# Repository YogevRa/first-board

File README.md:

# first-board: STM32G431 sensor development board

A 50 × 50 mm, 4-layer development board built around an STM32G431, with a temperature/humidity sensor, USB-C and SWD.
My first PCB: designed in KiCad 10, manufactured and assembled by JLCPCB.

Designed by Yogev Raz.

## Features

- **MCU:** STM32G431CBT6 (Arm Cortex-M4F, 170 MHz, 128 KB flash, 32 KB SRAM), LQFP-48, 12 MHz crystal
- **USB-C:** USB 2.0 full-speed device, USBLC6-2SC6 ESD protection on D+/D−, 5.1 kΩ CC pull-downs
- **Power:** 5 V from USB-C, AP2112K-3.3 LDO (600 mA)
- **Sensor:** Sensirion SHT40 (temperature and humidity, I²C address 0x44), thermally isolated from the rest of the board by an L-shaped slot
- **User I/O:** BOOT, RESET and USER buttons; PWR, STAT and ERR LEDs
- **Headers:** 6-pin SWD (3V3, CLK, GND, DIO, RST, SWO) and 8-pin expansion (3V3, GND, PA2–PA7)
- **Test points:** 5V, GND, 3V3
- **PCB:** 4 layers (signal / GND / 3V3 / signal), 4 × M3 mounting holes

## Documents

- [Schematic (PDF)](docs/first-board.pdf)

## Repository layout

| Path | Contents |
|---|---|
| `first-board.kicad_pro`, `.kicad_sch`, `.kicad_pcb` | KiCad 10 project |
| `first-board.pretty/` | Project footprint library (USB-C receptacle) |
| `first-board.ioc` | STM32CubeMX pin planning |
| `jlcpcb/` | Manufacturing files as sent to JLCPCB: Gerbers and drill files, BOM, CPL |
| `docs/` | Schematic PDF, design specification, renders |

## Manufacturing (v1.0)

- Ordered from JLCPCB in November 2026: 5 PCBs, 2 of them assembled (Economic PCBA)
- 35 SMD parts (16 part types) placed by JLCPCB; the SWD and expansion headers (J2, J3) are hand-soldered
- Rotation offsets between the KiCad footprints and the JLCPCB part library were corrected in the CPL file (U1, U2, U3)
- DRC and ERC clean at release

## Status

- [x] Schematic and layout
- [x] Ordered (v1.0)
- [ ] Bring-up
- [ ] Firmware

## Planned for v1.1

- TVS diode on VBUS and ESD protection on the CC lines
- RC network between the USB shield and GND
- Qwiic (I²C) connector
- Jumper for measuring board current
- Prefer JLCPCB Basic parts, and a stackup that Economic PCBA supports

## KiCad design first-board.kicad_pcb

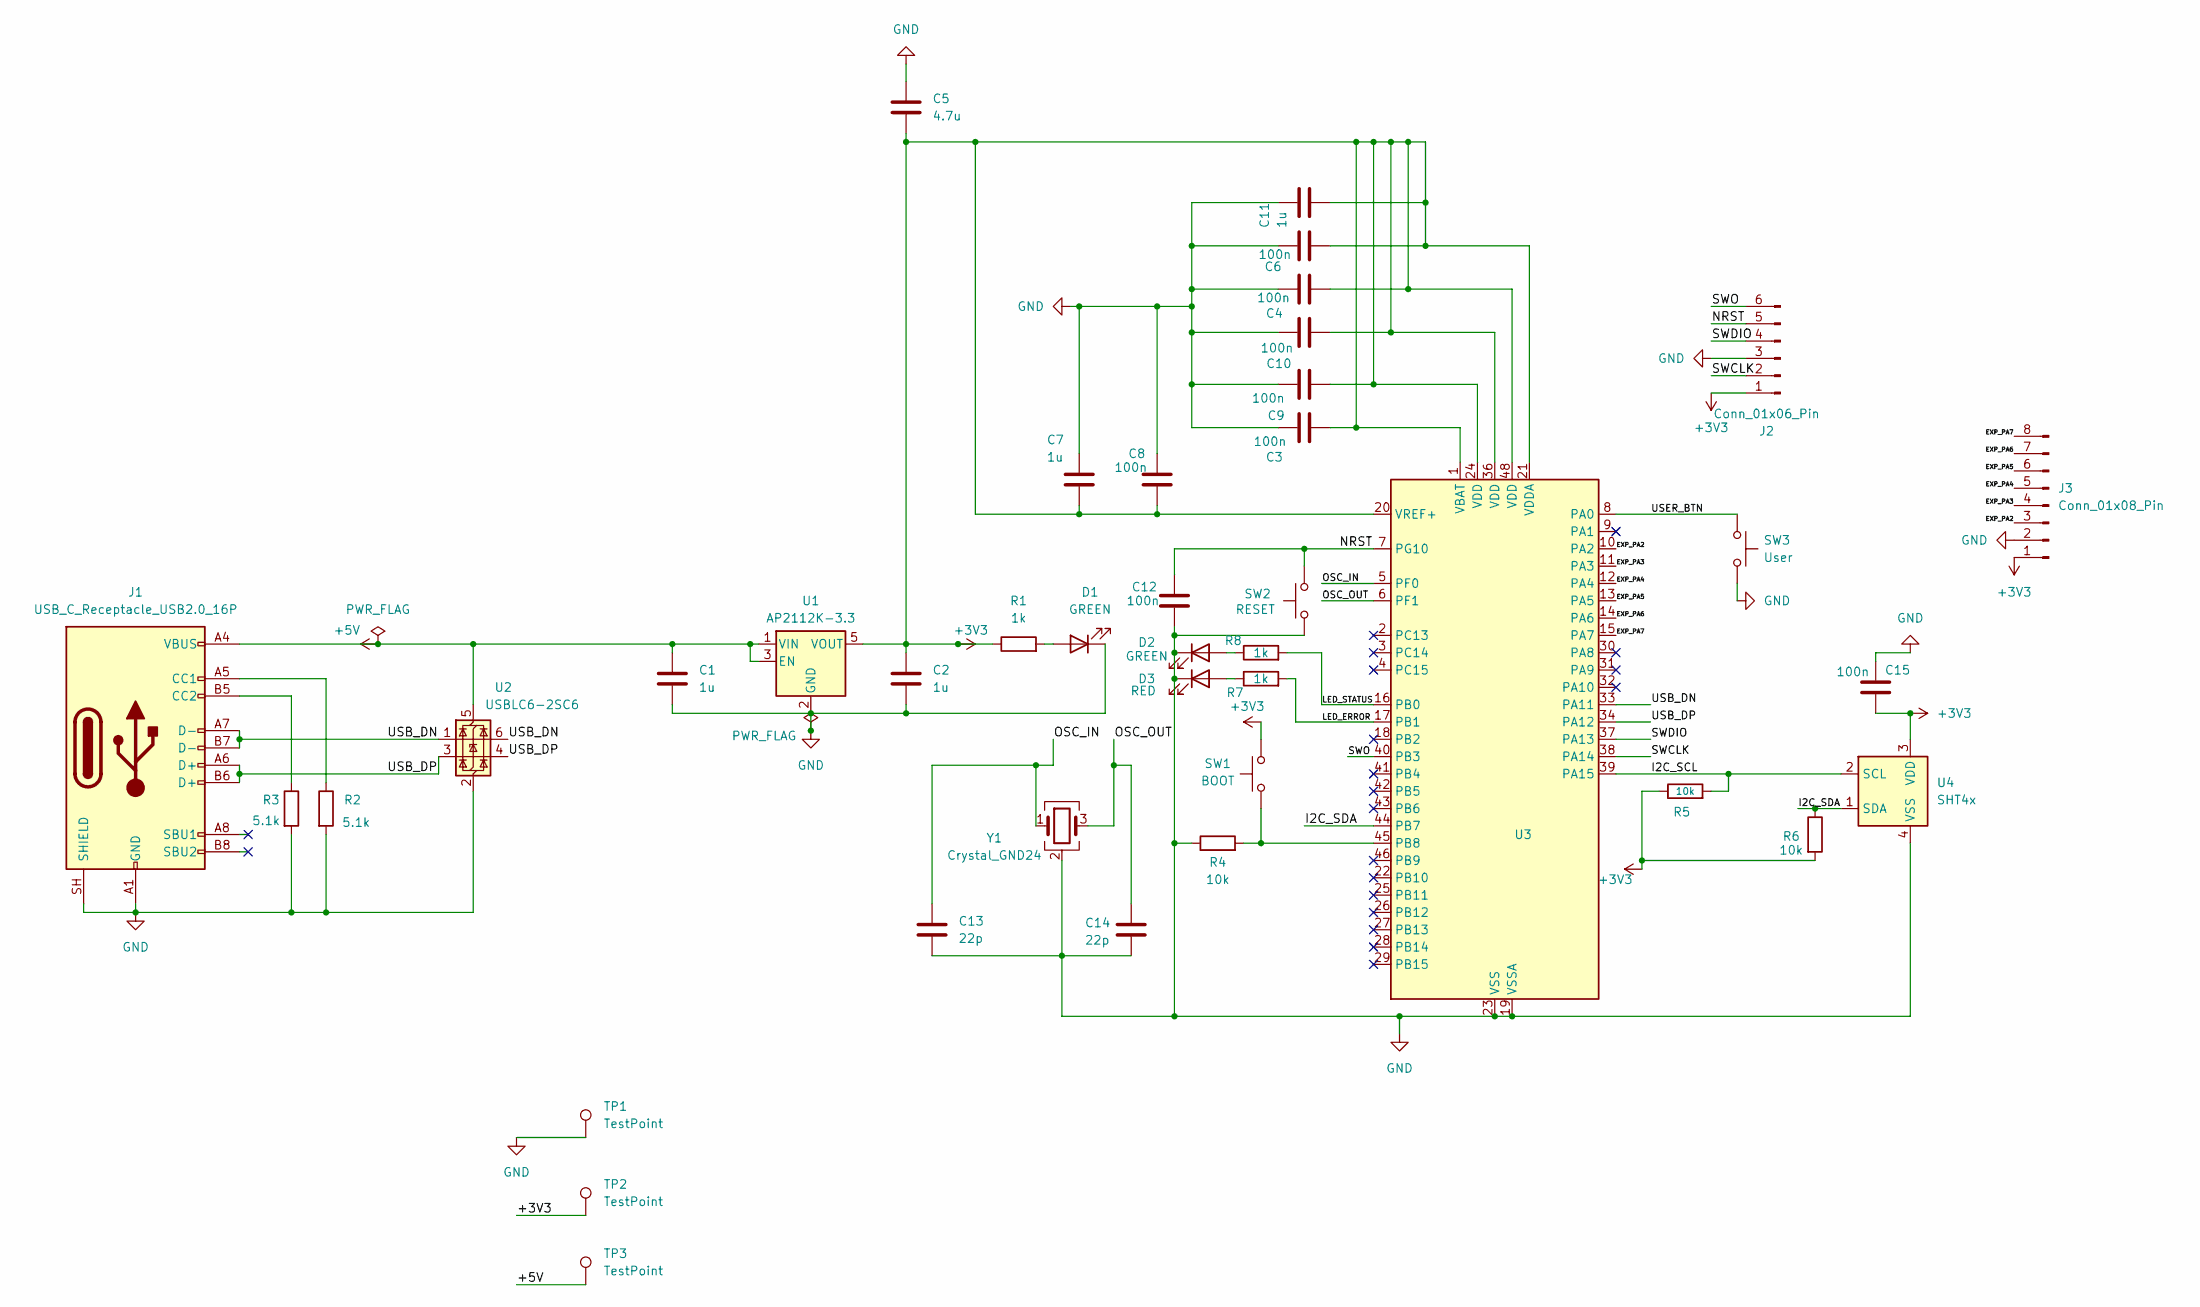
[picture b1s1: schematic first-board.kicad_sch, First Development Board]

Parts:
C1, C2, C7, C11: 1u; C_0603_1608Metric; LCSC Part # C15849
C3, C4, C6, C8, C9, C10, C12, C15: 100n; C_0603_1608Metric; LCSC Part # C14663
C5: 4.7u; C_0603_1608Metric; LCSC Part # C19666
C13, C14: 22p; C_0603_1608Metric; LCSC Part # C1653
D1, D2: GREEN; LED_0805_2012Metric; LCSC Part # C2297
D3: RED; LED_0603_1608Metric; LCSC Part # C2286
J1: USB_C_Receptacle_USB2.0_16P; USB_C_Receptacle_SHOUHAN_TYPE-C16PIN; LCSC Part # C393939
J2: Conn_01x06_Pin; PinHeader_1x06_P2.54mm_Vertical; LCSC Part # C492405
J3: Conn_01x08_Pin; PinHeader_1x08_P2.54mm_Vertical; LCSC Part # C492407
R1, R7, R8: 1k; R_0603_1608Metric; LCSC Part # C21190
R2, R3: 5.1k; R_0603_1608Metric; LCSC Part # C23186
R4, R5, R6: 10k; R_0603_1608Metric; LCSC Part # C25804
SW1: BOOT; SW_Push_1P1T_XKB_TS-1187A; LCSC Part # C318884
SW2: RESET; SW_Push_1P1T_XKB_TS-1187A; LCSC Part # C318884
SW3: User; SW_Push_1P1T_XKB_TS-1187A; LCSC Part # C318884
TP1, TP2, TP3: TestPoint; TestPoint_THTPad_D1.5mm_Drill0.7mm
U1: AP2112K-3.3; SOT-23-5; LCSC Part # C51118
U2: USBLC6-2SC6; SOT-23-6; LCSC Part # C7519
U3: STM32G431CBTx; LQFP-48_7x7mm_P0.5mm; LCSC Part # C529355
U4: SHT4x; Sensirion_DFN-4_1.5x1.5mm_P0.8mm_SHT4x_NoCentralPad; LCSC Part # C2848306
Y1: Crystal_GND24; Crystal_SMD_3225-4Pin_3.2x2.5mm; LCSC Part # C9002

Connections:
+3V3: C2.2, C3.2, C4.2, C5.1, C6.2, C7.1, C8.1, C9.2, C10.2, C11.1, C15.1, J2.1, J3.1, R1.1, R5.1, R6.2, SW1.2, TP2.1 (1_1), U1.5 (VOUT), U3.1 (VBAT), U3.20 (VREF+), U3.21 (VDDA), U3.24 (VDD), U3.36 (VDD), U3.48 (VDD), U4.3 (VDD)
+5V: C1.2, J1.A4 (VBUS), J1.A9 (VBUS), J1.B4 (VBUS), J1.B9 (VBUS), TP3.1 (1_1), U1.1 (VIN), U1.3 (EN), U2.5 (VBUS)
/EXP_PA2: J3.3, U3.10 (PA2)
/EXP_PA3: J3.4, U3.11 (PA3)
/EXP_PA4: J3.5, U3.12 (PA4)
/EXP_PA5: J3.6, U3.13 (PA5)
/EXP_PA6: J3.7, U3.14 (PA6)
/EXP_PA7: J3.8, U3.15 (PA7)
/I2C_SCL: R5.2, U3.39 (PA15), U4.2 (SCL)
/I2C_SDA: R6.1, U3.44 (PB7), U4.1 (SDA)
/LED_ERROR: R7.2, U3.17 (PB1)
/LED_STATUS: R8.2, U3.16 (PB0)
/NRST: C12.1, J2.5, SW2.2, U3.7 (PG10)
/OSC_IN: C13.1, U3.5 (PF0), Y1.1
/OSC_OUT: C14.1, U3.6 (PF1), Y1.3
/SWCLK: J2.2, U3.38 (PA14)
/SWDIO: J2.4, U3.37 (PA13)
/SWO: J2.6, U3.40 (PB3)
/USB_DN: J1.A7 (D-), J1.B7 (D-), U2.1 (I/O1), U2.6 (I/O1), U3.33 (PA11)
/USB_DP: J1.A6 (D+), J1.B6 (D+), U2.3 (I/O2), U2.4 (I/O2), U3.34 (PA12)
/USER_BTN: SW3.1, U3.8 (PA0)
GND: C1.1, C2.1, C3.1, C4.1, C5.2, C6.1, C7.2, C8.2, C9.1, C10.1, C11.2, C12.2, C13.2, C14.2, C15.2, D1.1 (K), D2.1 (K), D3.1 (K), J1.A1 (GND), J1.A12 (GND), J1.B1 (GND), J1.B12 (GND), J1.SH (SHIELD), J2.3, J3.2, R2.2, R3.2, R4.1, SW2.1, SW3.2, TP1.1 (1_1), U1.2 (GND), U2.2 (GND), U3.19 (VSSA), U3.23 (VSS), U3.35 (VSS), U3.47 (VSS), U4.4 (VSS), Y1.2 (G), Y1.4 (G)
unnamed: D1.2 (A), R1.2
unnamed: D2.2 (A), R8.1
unnamed: D3.2 (A), R7.1
unnamed: J1.A5 (CC1), R2.1
unnamed: J1.B5 (CC2), R3.1
unnamed: R4.2, SW1.1, U3.45 (PB8)

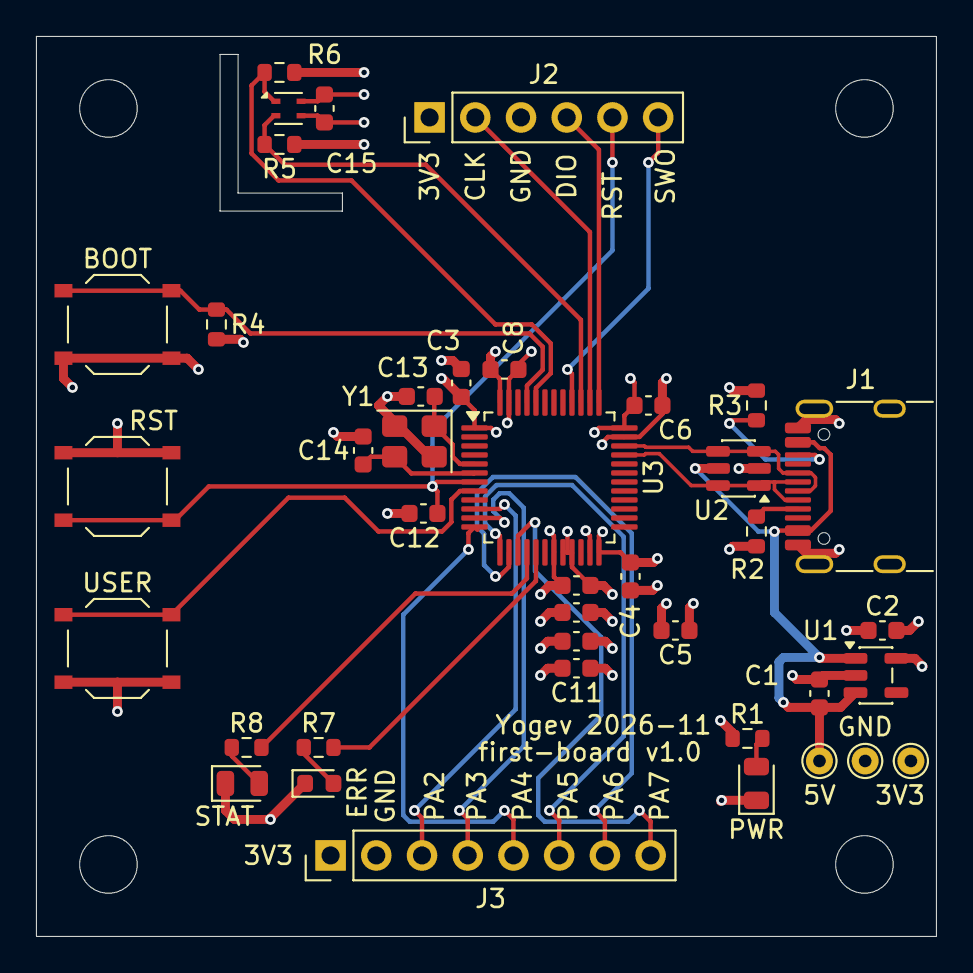
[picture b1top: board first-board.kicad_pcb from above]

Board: 4 copper layers, 50.0 x 50.0 mm, 44 parts (0 on the bottom side), 28 nets.

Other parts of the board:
H1, H2, H3, H4: MountingHole_3.2mm_M3

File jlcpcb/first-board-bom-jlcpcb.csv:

Comment,Designator,Footprint,LCSC Part #,Quantity
1u,"C1,C2,C7,C11",C_0603_1608Metric,C15849,4
100n,"C3,C4,C6,C8,C9,C10,C12,C15",C_0603_1608Metric,C14663,8
4.7u,C5,C_0603_1608Metric,C19666,1
22p,"C13,C14",C_0603_1608Metric,C1653,2
Green LED,"D1,D2",LED_0805_2012Metric,C2297,2
Red LED,D3,LED_0603_1608Metric,C2286,1
USB-C 16P (TYPE-C16PIN),J1,USB_C_Receptacle_SHOUHAN_TYPE-C16PIN,C393939,1
Header 1x6 2.54mm,J2,PinHeader_1x06_P2.54mm_Vertical,C492405,1
Header 1x8 2.54mm,J3,PinHeader_1x08_P2.54mm_Vertical,C492407,1
1k,"R1,R7,R8",R_0603_1608Metric,C21190,3
5.1k,"R2,R3",R_0603_1608Metric,C23186,2
10k,"R4,R5,R6",R_0603_1608Metric,C25804,3
TS-1187A-B-A-B,"SW1,SW2,SW3",SW_Push_1P1T_XKB_TS-1187A,C318884,3
AP2112K-3.3TRG1,U1,SOT-23-5,C51118,1
USBLC6-2SC6,U2,SOT-23-6,C7519,1
STM32G431CBT6,U3,LQFP-48_7x7mm_P0.5mm,C529355,1
SHT40-AD1B-R3,U4,Sensirion_DFN-4_1.5x1.5mm_P0.8mm_SHT4x_NoCentralPad,C2848306,1
12MHz,Y1,Crystal_SMD_3225-4Pin_3.2x2.5mm,C9002,1

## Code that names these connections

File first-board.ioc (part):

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Mcu.Name=STM32G431C(6-8-B)Tx
Mcu.Package=LQFP48
Mcu.UserName=STM32G431CBTx
PA0.GPIOParameters=GPIO_Label
PA0.GPIO_Label=USER_BTN
PA0.Signal=GPIO_Input
PA11.Mode=Device
PA11.Signal=USB_DM
PA12.Mode=Device
PA12.Signal=USB_DP
PA13.Mode=Trace_Asynchronous_SW
PA13.Signal=SYS_JTMS-SWDIO
PA14.Mode=Trace_Asynchronous_SW
PA14.Signal=SYS_JTCK-SWCLK
PA15.Mode=I2C
PA15.Signal=I2C1_SCL
PA2.Mode=Asynchronous
PA2.Signal=USART2_TX
PA3.Mode=Asynchronous
PA3.Signal=USART2_RX
PA5.Mode=Full_Duplex_Master
PA5.Signal=SPI1_SCK
PA6.Mode=Full_Duplex_Master
PA6.Signal=SPI1_MISO
PA7.Mode=Full_Duplex_Master
PA7.Signal=SPI1_MOSI
PB0.GPIOParameters=GPIO_Label
PB0.GPIO_Label=LED_STATUS
PB0.Signal=GPIO_Output
PB1.GPIOParameters=GPIO_Label
PB1.GPIO_Label=LED_ERROR
PB1.Signal=GPIO_Output
PB3.Mode=Trace_Asynchronous_SW
PB3.Signal=SYS_JTDO-SWO
PB7.Mode=I2C
PB7.Signal=I2C1_SDA
PF0-OSC_IN.Mode=HSE-External-Oscillator
PF0-OSC_IN.Signal=RCC_OSC_IN
PF1-OSC_OUT.Mode=HSE-External-Oscillator
PF1-OSC_OUT.Signal=RCC_OSC_OUT
RCC.HSE_VALUE=12000000
RCC.SYSCLKFreq_VALUE=144000000
RCC.SYSCLKSource=RCC_SYSCLKSOURCE_PLLCLK
board=custom
